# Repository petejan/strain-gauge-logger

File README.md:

# strain-gauge-logger

Logging for adc122c04 24 bit ADC using arduino/SAMD21.

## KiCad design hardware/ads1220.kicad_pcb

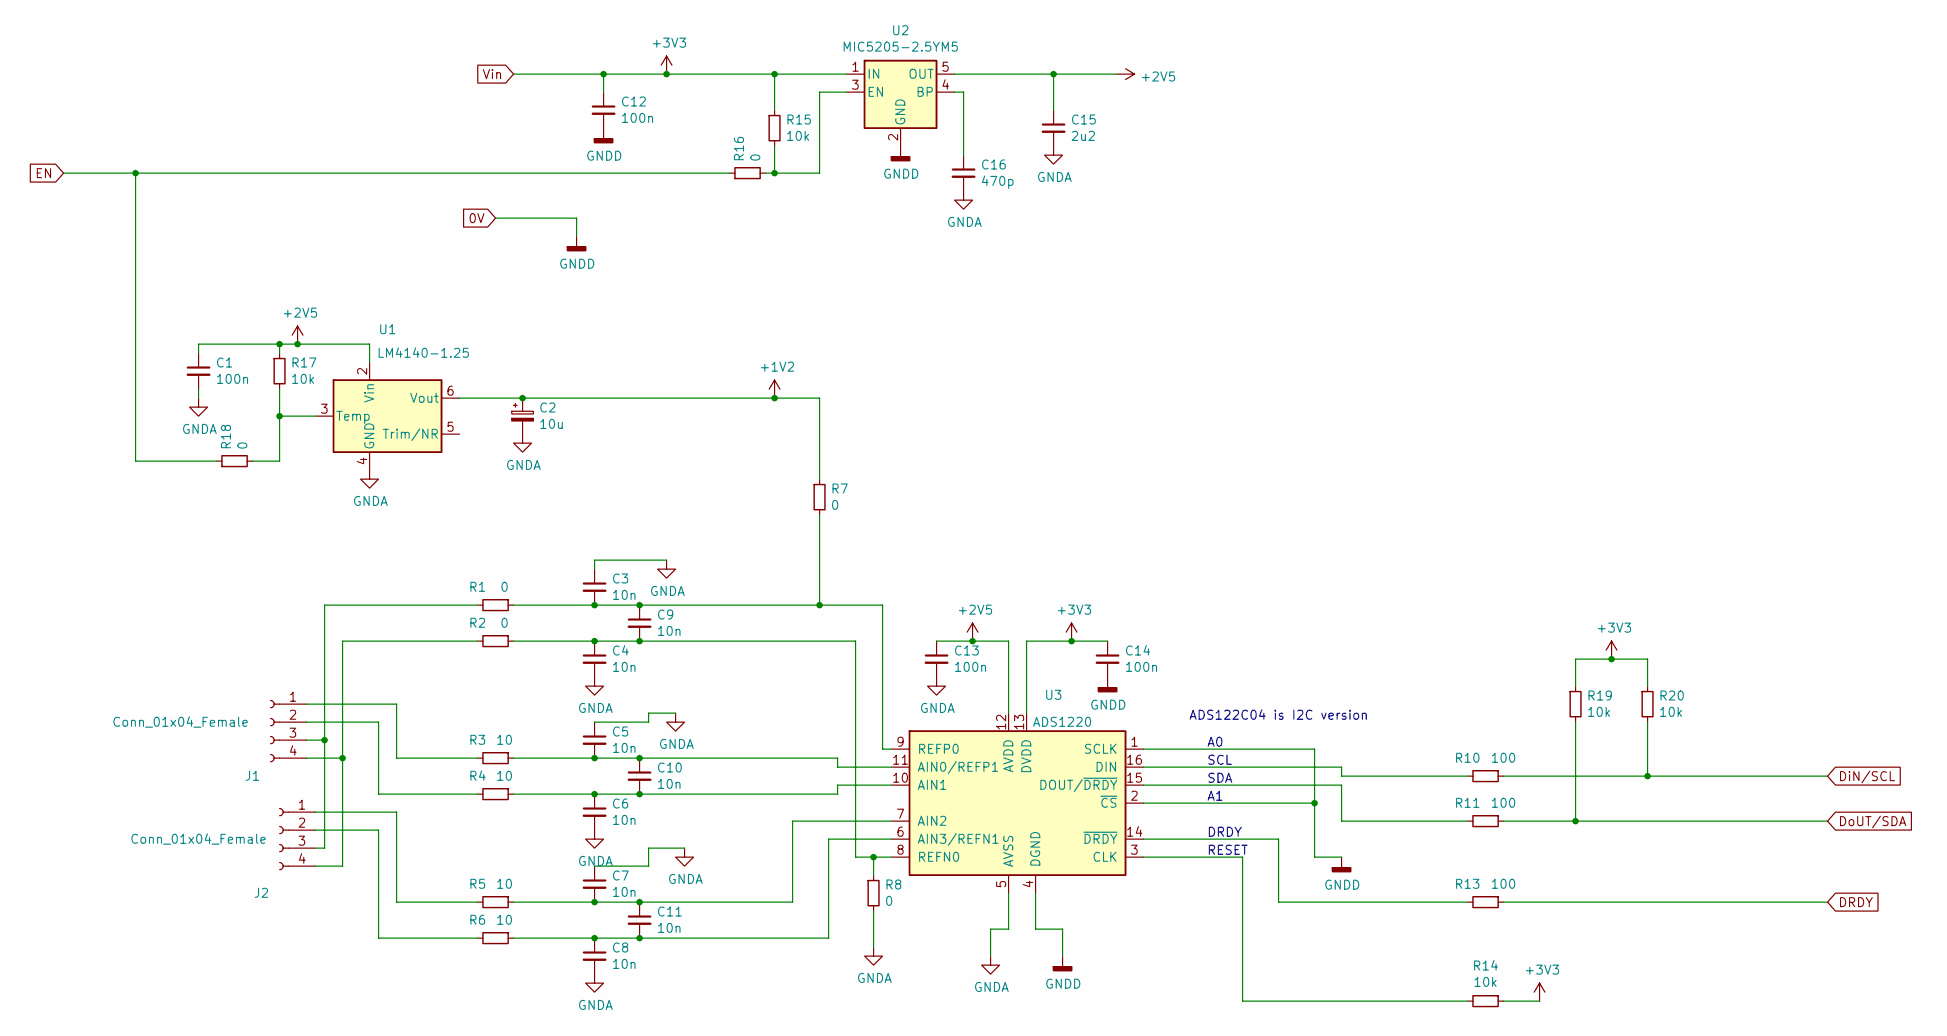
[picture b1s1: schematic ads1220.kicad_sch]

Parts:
C1, C12, C13, C14: 100n; C_0805_2012Metric_Pad1.18x1.45mm_HandSolder
C2: 10u; C_0805_2012Metric_Pad1.18x1.45mm_HandSolder
C3, C4, C5, C6, C7, C8, C9, C10, C11: 10n; C_0805_2012Metric_Pad1.18x1.45mm_HandSolder
C15: 2u2; C_0805_2012Metric_Pad1.18x1.45mm_HandSolder
C16: 470p; C_0805_2012Metric_Pad1.15x1.40mm_HandSolder
J1, J2: Conn_01x04_Female; Molex_Nano-Fit_105314-xx04_2x02_P2.50mm_Horizontal
R1, R2, R7, R8, R16, R18: 0; R_0805_2012Metric_Pad1.20x1.40mm_HandSolder
R3, R4, R5, R6: 10; R_0805_2012Metric_Pad1.20x1.40mm_HandSolder
R10, R11, R13: 100; R_0805_2012Metric_Pad1.20x1.40mm_HandSolder
R14, R15, R17, R19, R20: 10k; R_0805_2012Metric_Pad1.20x1.40mm_HandSolder
U1: LM4140-1.25; SOIC-8_3.9x4.9mm_P1.27mm
U2: MIC5205-2.5YM5; SOT-23-5
U3: ADS1220; TSSOP-16_4.4x5mm_P0.65mm

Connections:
0V: C12.2, C14.2, U2.2 (GND), U3.1 (SCLK), U3.2 (~CS), U3.4 (DGND)
+1V2: C2.1, R7.1, U1.6 (Vout)
+2V5: C1.1, C13.1, C15.1, R17.1, U1.2 (Vin), U2.5 (OUT), U3.12 (AVDD)
DRDY: R13.1
DiN/SCL: R10.1, R20.2
DoUT/SDA: R11.1, R19.2
EN: R16.1, R18.1
GNDA: C1.2, C2.2, C3.1, C4.2, C5.1, C6.2, C7.1, C8.2, C13.2, C15.2, C16.2, R8.2, U1.4 (GND), U3.5 (AVSS)
unnamed: J1.1, R3.2
unnamed: J1.2, R4.2
unnamed: J1.3, J2.3, R1.2
unnamed: J1.4, J2.4, R2.2
unnamed: J2.1, R5.2
unnamed: J2.2, R6.2
unnamed: R17.2, R18.2, U1.3 (Temp)
unnamed: C16.1, U2.4 (BP)
unnamed: R15.2, R16.2, U2.3 (EN)
unnamed: C5.2, C10.1, R3.1, U3.11 (AIN0/REFP1)
unnamed: C6.1, C10.2, R4.1, U3.10 (AIN1)
unnamed: C7.2, C11.1, R5.1, U3.7 (AIN2)
unnamed: C8.1, C11.2, R6.1, U3.6 (AIN3/REFN1)
unnamed: R14.2, U3.3 (CLK)
unnamed: R10.2, U3.16 (DIN)
unnamed: R11.2, U3.15 (DOUT/~DRDY)
unnamed: C4.1, C9.2, R2.1, R8.1, U3.8 (REFN0)
unnamed: C3.2, C9.1, R1.1, R7.2, U3.9 (REFP0)
unnamed: R13.2, U3.14 (~DRDY)
Vin: C12.1, C14.1, R14.1, R15.1, R19.1, R20.1, U2.1 (IN), U3.13 (DVDD)

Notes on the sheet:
SDA
ADS122C04 is I2C version
RESET
DRDY
SCL

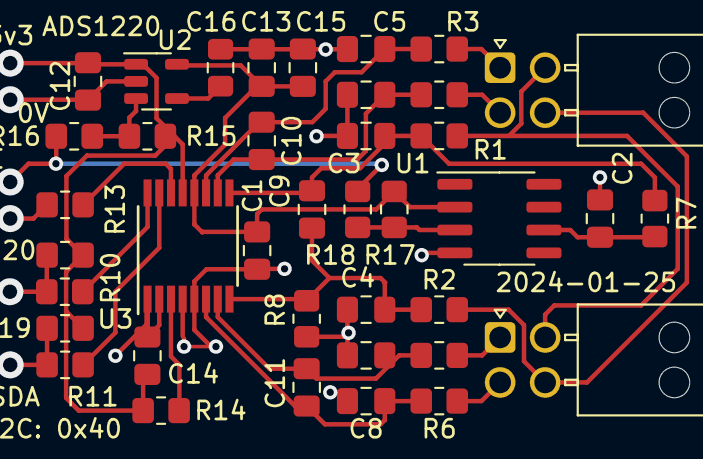
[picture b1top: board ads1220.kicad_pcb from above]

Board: 2 copper layers, 39 parts (0 on the bottom side), 27 nets.

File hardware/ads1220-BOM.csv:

"Reference","Qty","Value","DNP","Exclude from BOM","Exclude from Board","Footprint","Datasheet"
"C1,C12,C13,C14","4","100n","","","","Capacitor_SMD:C_0805_2012Metric_Pad1.18x1.45mm_HandSolder","~"
"C2","1","10u","","","","Capacitor_SMD:C_0805_2012Metric_Pad1.18x1.45mm_HandSolder","~"
"C3,C4,C5,C6,C7,C8,C9,C10,C11","9","10n","","","","Capacitor_SMD:C_0805_2012Metric_Pad1.18x1.45mm_HandSolder","~"
"C15","1","2u2","","","","Capacitor_SMD:C_0805_2012Metric_Pad1.18x1.45mm_HandSolder","~"
"C16","1","470p","","","","Capacitor_SMD:C_0805_2012Metric_Pad1.15x1.40mm_HandSolder","~"
"J1,J2","2","Conn_01x04_Female","","","","Connector_Molex:Molex_Nano-Fit_105314-xx04_2x02_P2.50mm_Horizontal","~"
"R1,R2,R7,R8,R16,R18","6","0","","","","Resistor_SMD:R_0805_2012Metric_Pad1.20x1.40mm_HandSolder","~"
"R3,R4,R5,R6","4","10","","","","Resistor_SMD:R_0805_2012Metric_Pad1.20x1.40mm_HandSolder","~"
"R10,R11,R13","3","100","","","","Resistor_SMD:R_0805_2012Metric_Pad1.20x1.40mm_HandSolder","~"
"R14,R15,R17,R19,R20","5","10k","","","","Resistor_SMD:R_0805_2012Metric_Pad1.20x1.40mm_HandSolder","~"
"U1","1","LM4140-1.25","","","","Package_SO:SOIC-8_3.9x4.9mm_P1.27mm","http://www.ti.com/lit/ds/symlink/ref5030.pdf"
"U2","1","MIC5205-2.5YM5","","","","Package_TO_SOT_SMD:SOT-23-5","http://ww1.microchip.com/downloads/en/DeviceDoc/20005785A.pdf"
"U3","1","ADS1220","","","","Package_SO:TSSOP-16_4.4x5mm_P0.65mm","http://www.ti.com/lit/ds/symlink/ads1120.pdf"

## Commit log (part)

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2024-01-02 initial commit
    commit of code deployed for KELP project
2024-01-02 add docs and hardware
2024-01-04 commit baseline arduino
    Changes files for 8 MHz osc
2024-01-04 changes for 8 MHz osc
    modifty build and feather.m0 and qtpy
2024-01-04 datasheets and PCB mod to molex-minifit connector
2024-01-07 changes for QTPY
    change I2C port, and clocks, less Digital PINs
2024-01-09 Update adc122c04_direct.ino
    change external interrupt system clock to GEN02 so it runs in sleep mode.
2024-01-09 commit changes to arduioPlugin
    boards, startup and LowPower library changes
2024-01-09 Update adc122c04_direct.ino
    typo fix
2024-01-09 Update adc122c04_direct.ino
    allow faster sampling rate, 4 = 5 ms sampling with reg1 = 192
2024-01-10 Update adc122c04_direct.ino
    changes for continuous mode
2024-01-11 Update adc122c04_direct.ino
    change to LOW interrupt trigger as can be asynchronous with GCLK
2024-01-12 Update adc122c04_direct.ino
    try fix missing samples in continuous mode
2024-01-12 Update adc122c04_direct.ino
    allow for 48 MHz clock
2024-01-16 found delayed adc reads, due to RTC sync delay
2024-01-16 Update adc122c04_direct.ino
    update data rate cala, fix time reg upates
2024-01-24 changes for DMA I2C transfers
    inititaly just RDATA uses DMA. SDcard uses 2 DMA channels
2024-01-24 Update sloeber.ino.cpp
    changes for DMA
2024-01-25 hardware updates
2024-01-30 Update adc122c04_direct.ino
    add code to recode time set and run time
2024-01-30 Update adc122c04_direct.ino
    add bytes/sample configuration
2024-02-01 Update adc122c04_direct.ino
    change to 3 bytes/sample
2024-02-01 Update adc122c04_direct.ino
    document I2C baud rate
2024-02-01 fixup LowPower Lib
    Don't use fixed library
2024-02-01 fixup libraries
2024-02-01 commit PCB
2024-02-04 no DMA config
2024-02-12 disable I2C when sleep
    I2C pul up on SDA draw current in sleep mode.
2024-02-14 Update adc122c04_direct.ino
    add check for IDLE before sleep, causes missed samples
2024-02-18 add burst sampling
    add nburst to sampling
2024-02-18 Update adc122c04_direct.ino
    add burst mode to continuous mode
2024-02-18 Update sloeber.ino.cpp
    add cmd_burst
2024-02-18 fix burst mode, add ITSYBITSY option
2024-02-22 work on ITSYBITSY version
    writes to FLASH working
2024-02-22 Update .gitignore
    add DS_Store
2024-02-25 add zmodem upload/download files
2024-03-02 add sensor detect mode
    Add RUN_MODE_DETECT
    change all prints to printf
    zmodem transfers
2024-03-03 sentron config
    add RUN_MODE_DETECT to documentation
2024-03-03 fixed to python reader
2024-03-05 Update adc122c04_direct.ino
    fix decrease input detection level
2024-03-18 divide main file into adc/i2c/timer/cmd
    separate functions from main source file
2024-03-22 fix flash storage definitions
2026-01-05 add BOM list
